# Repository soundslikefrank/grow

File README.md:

# GROW

A Eurorack genetic sequencer.

This repository serves as the home for its MCU code and hardware schematics.

There will be a lot more info soon.

## To build

```sh
git submodule update --init --recursive # if not cloned recursively
brew install cmake
brew install --cask gcc-arm-embedded
mkdir build && cd build
cmake -DCMAKE_TOOLCHAIN_FILE=../arm-none-eabi-gcc.cmake ..
make
```

## LICENSE

GNU General Public License v3.0

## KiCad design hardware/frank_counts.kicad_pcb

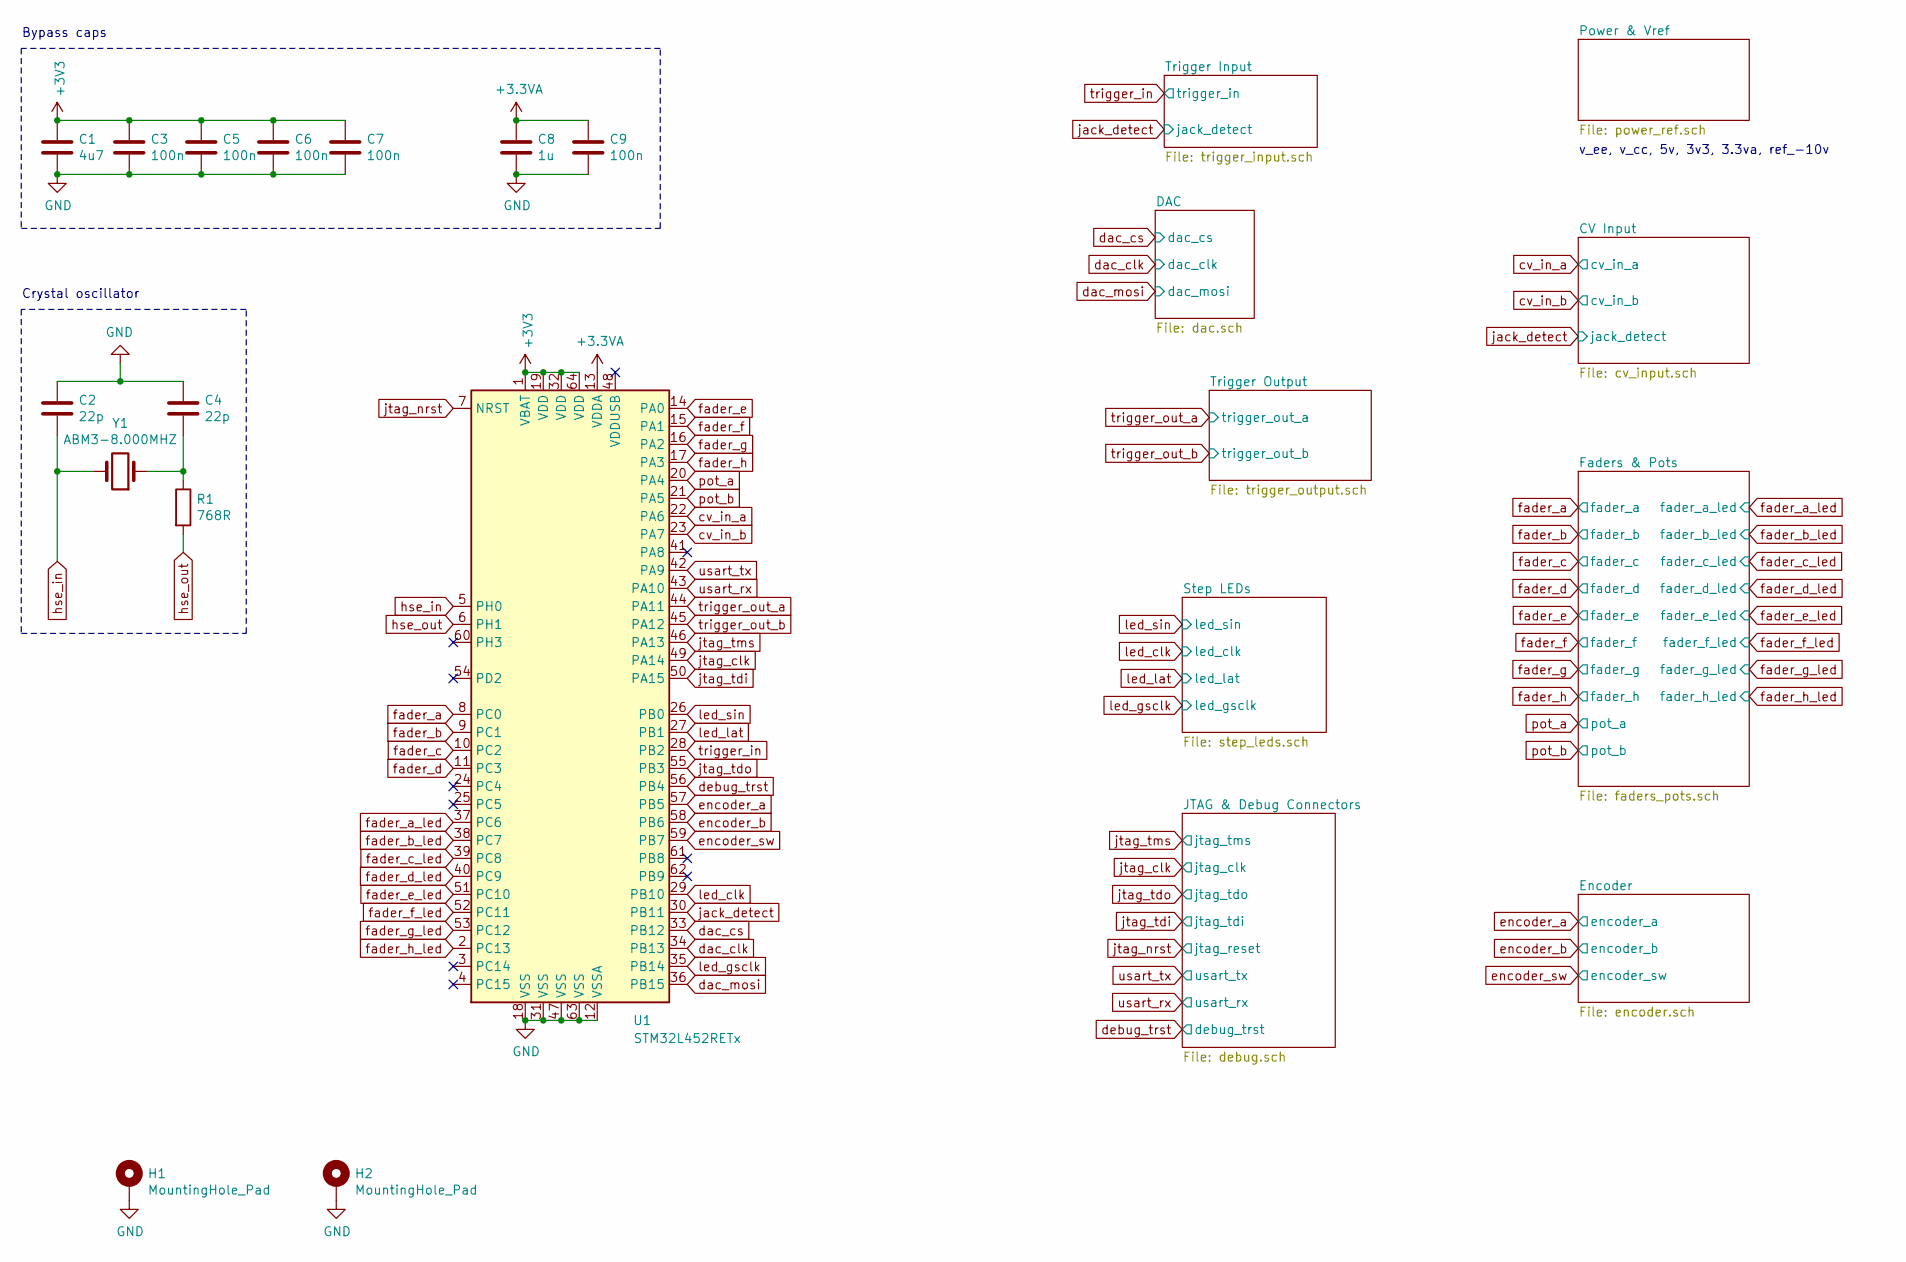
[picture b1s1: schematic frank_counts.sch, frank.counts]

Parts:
C1: 4u7; C_0603_1608Metric
C2, C4: 22p; C_0603_1608Metric
C3, C5, C6, C7, C9: 100n; C_0603_1608Metric
C8: 1u; C_0603_1608Metric
H1, H2: MountingHole_Pad; MountingHole_3.2mm_M3
R1: 768R; R_0603_1608Metric
U1: STM32L452RETx; LQFP-64_10x10mm_P0.5mm
Y1: ABM3-8.000MHZ; Crystal_SMD_Abracon_ABM3-2Pin_5.0x3.2mm_HandSoldering

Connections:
GND: C1.2, C2.1, C3.2, C4.1, C5.2, C6.2, C7.2, C8.2, C9.2, H1.1, H2.1, U1.12 (VSSA), U1.18 (VSS), U1.31 (VSS), U1.47 (VSS), U1.63 (VSS); also elsewhere on the board
unnamed: C4.2, R1.1, Y1.1
cv_in_a: U1.22 (PA6); also elsewhere on the board
cv_in_b: U1.23 (PA7); also elsewhere on the board
dac_avdd: C8.1, C9.1, U1.13 (VDDA); also elsewhere on the board
dac_clk: U1.34 (PB13); also elsewhere on the board
dac_cs: U1.33 (PB12); also elsewhere on the board
dac_mosi: U1.36 (PB15); also elsewhere on the board
debug_trst: U1.56 (PB4); also elsewhere on the board
encoder_a: U1.57 (PB5); also elsewhere on the board
encoder_b: U1.58 (PB6); also elsewhere on the board
encoder_sw: U1.59 (PB7); also elsewhere on the board
fader_a: U1.8 (PC0); also elsewhere on the board
fader_a_led: U1.37 (PC6); also elsewhere on the board
fader_b: U1.9 (PC1); also elsewhere on the board
fader_b_led: U1.38 (PC7); also elsewhere on the board
fader_c: U1.10 (PC2); also elsewhere on the board
fader_c_led: U1.39 (PC8); also elsewhere on the board
fader_d: U1.11 (PC3); also elsewhere on the board
fader_d_led: U1.40 (PC9); also elsewhere on the board
fader_e: U1.14 (PA0); also elsewhere on the board
fader_e_led: U1.51 (PC10); also elsewhere on the board
fader_f: U1.15 (PA1); also elsewhere on the board
fader_f_led: U1.52 (PC11); also elsewhere on the board
fader_g: U1.16 (PA2); also elsewhere on the board
fader_g_led: U1.53 (PC12); also elsewhere on the board
fader_h: U1.17 (PA3); also elsewhere on the board
fader_h_led: U1.2 (PC13); also elsewhere on the board
hse_in: C2.2, U1.5 (PH0), Y1.2
hse_out: R1.2, U1.6 (PH1)
jack_detect: U1.30 (PB11); also elsewhere on the board
jtag_clk: U1.49 (PA14); also elsewhere on the board
jtag_nrst: U1.7 (NRST); also elsewhere on the board
jtag_tdi: U1.50 (PA15); also elsewhere on the board
jtag_tdo: U1.55 (PB3); also elsewhere on the board
jtag_tms: U1.46 (PA13); also elsewhere on the board
led_clk: U1.29 (PB10); also elsewhere on the board
led_gsclk: U1.35 (PB14); also elsewhere on the board
led_lat: U1.27 (PB1); also elsewhere on the board
led_sin: U1.26 (PB0); also elsewhere on the board
pot_a: U1.20 (PA4); also elsewhere on the board
pot_b: U1.21 (PA5); also elsewhere on the board
trigger_in: U1.28 (PB2); also elsewhere on the board
trigger_out_a: U1.44 (PA11); also elsewhere on the board
trigger_out_b: U1.45 (PA12); also elsewhere on the board
usart_rx: U1.43 (PA10); also elsewhere on the board
usart_tx: U1.42 (PA9); also elsewhere on the board

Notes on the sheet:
Bypass caps
Crystal oscillator
v_ee, v_cc, 5v, 3v3, 3.3va, ref_-10v

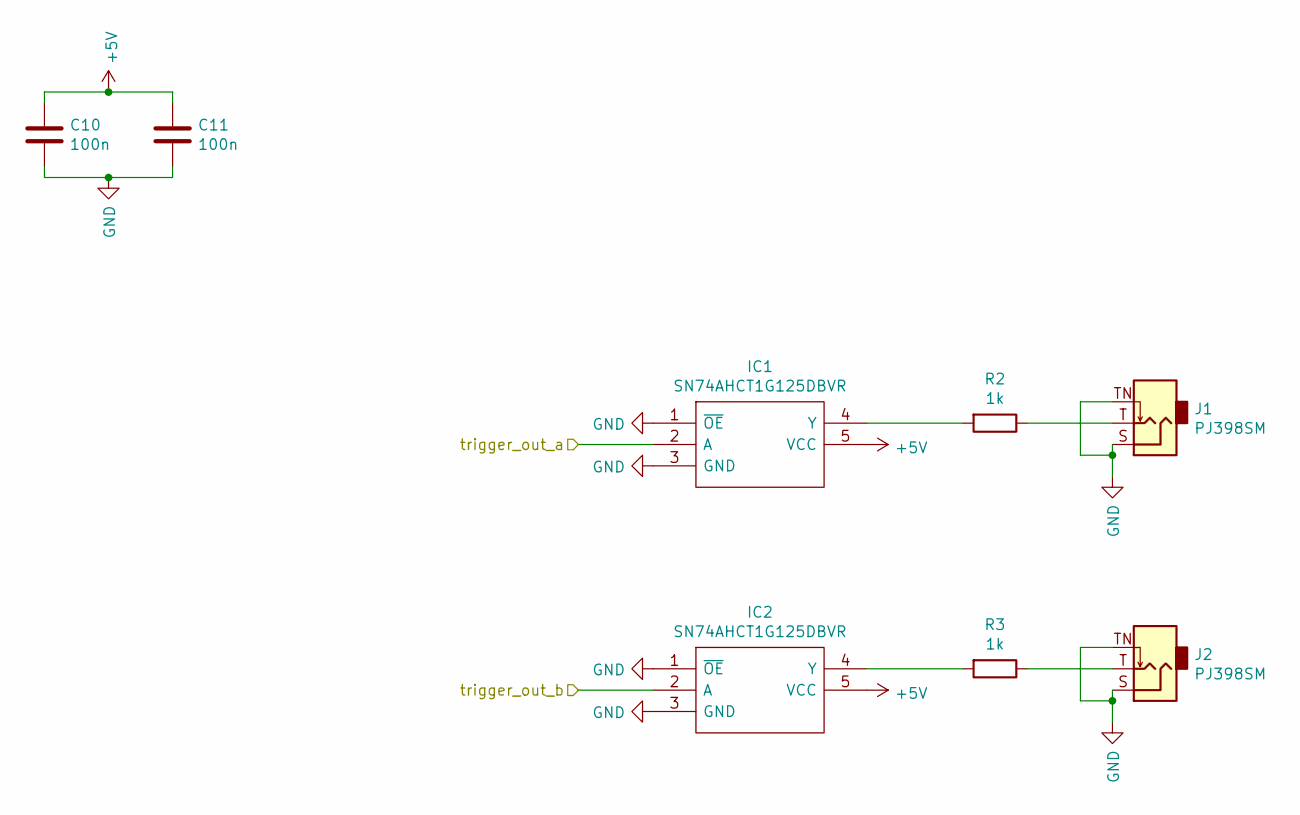
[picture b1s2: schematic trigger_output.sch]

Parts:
C10, C11: 100n; C_0603_1608Metric
IC1, IC2: SN74AHCT1G125DBVR; SOT95P280X145-5N; Manufacturer_Part_Number SN74AHCT1G125DBVR; Mouser Part Number 595-SNAHCT1G125DBVR
J1, J2: PJ398SM; Jack_3.5mm_QingPu_WQP-PJ398SM_Vertical_CircularHoles
R2, R3: 1k; R_0603_1608Metric

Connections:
+5V: C10.1, C11.1, IC1.5 (VCC), IC2.5 (VCC); also elsewhere on the board
GND: C10.2, C11.2, IC1.1 (~OE), IC1.3 (GND), IC2.1 (~OE), IC2.3 (GND), J1.S, J1.TN, J2.S, J2.TN; also elsewhere on the board
unnamed: IC1.4 (Y), R2.2
unnamed: IC2.4 (Y), R3.2
unnamed: J1.T, R2.1
unnamed: J2.T, R3.1
trigger_out_a: IC1.2 (A); also elsewhere on the board
trigger_out_b: IC2.2 (A); also elsewhere on the board

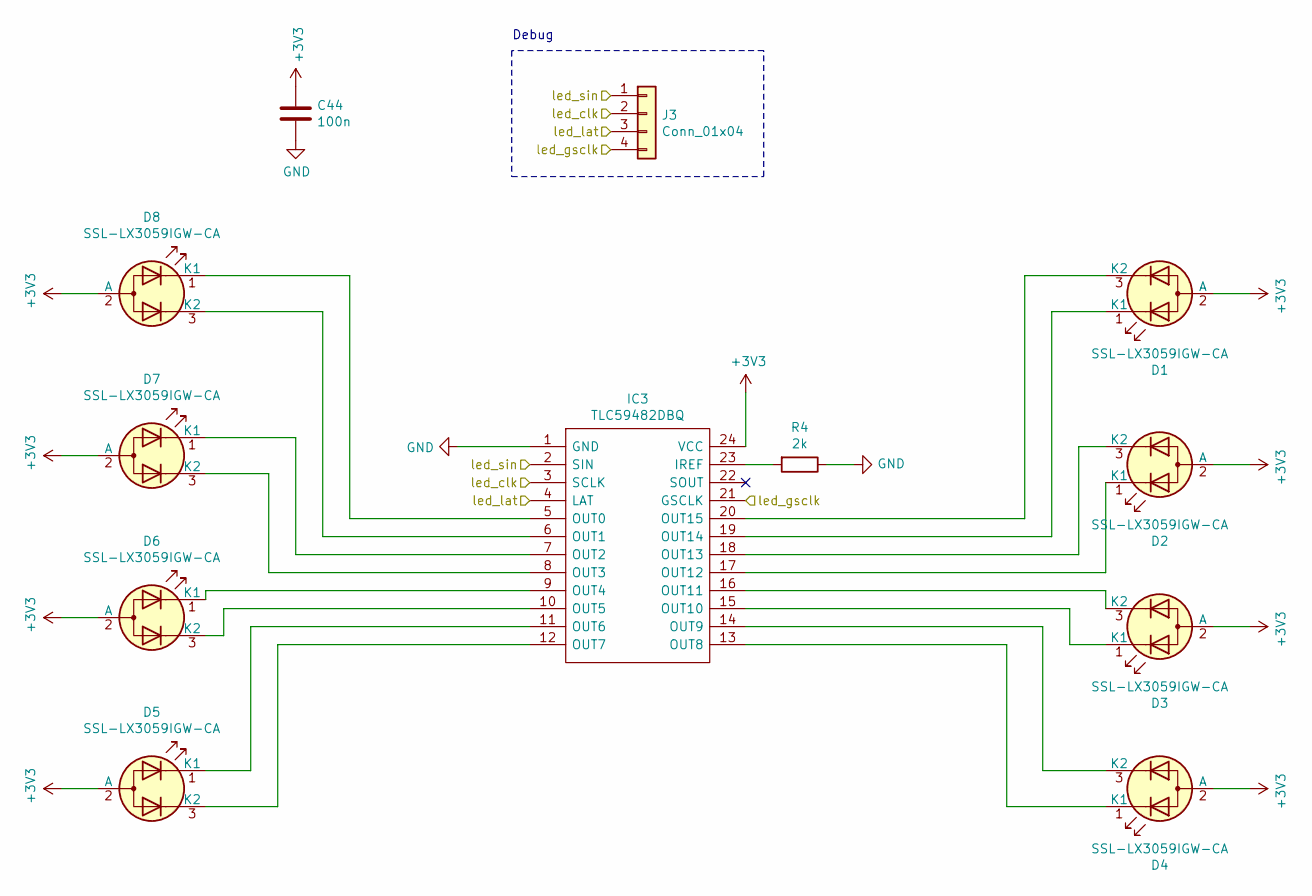
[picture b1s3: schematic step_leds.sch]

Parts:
C44: 100n; C_0603_1608Metric
D1, D2, D3, D4, D5, D6, D7, D8: SSL-LX3059IGW-CA; LED_D3.0mm-3
IC3: TLC59482DBQ; SOP64P600X175-24N; Manufacturer_Part_Number TLC59482DBQ; Mouser Part Number 595-TLC59482DBQ
J3: Conn_01x04; PinHeader_1x04_P2.54mm_Vertical
R4: 2k; R_0603_1608Metric

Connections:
GND: C44.2, IC3.1 (GND), R4.1; also elsewhere on the board
unnamed: D1.1 (K1), IC3.19 (OUT14)
unnamed: D1.3 (K2), IC3.20 (OUT15)
unnamed: D2.1 (K1), IC3.17 (OUT12)
unnamed: D2.3 (K2), IC3.18 (OUT13)
unnamed: D3.1 (K1), IC3.15 (OUT10)
unnamed: D3.3 (K2), IC3.16 (OUT11)
unnamed: D4.1 (K1), IC3.13 (OUT8)
unnamed: D4.3 (K2), IC3.14 (OUT9)
unnamed: D5.1 (K1), IC3.11 (OUT6)
unnamed: D5.3 (K2), IC3.12 (OUT7)
unnamed: D6.1 (K1), IC3.9 (OUT4)
unnamed: D6.3 (K2), IC3.10 (OUT5)
unnamed: D7.1 (K1), IC3.7 (OUT2)
unnamed: D7.3 (K2), IC3.8 (OUT3)
unnamed: D8.1 (K1), IC3.5 (OUT0)
unnamed: D8.3 (K2), IC3.6 (OUT1)
unnamed: IC3.23 (IREF), R4.2
led_clk: IC3.3 (SCLK), J3.2; also elsewhere on the board
led_gsclk: IC3.21 (GSCLK), J3.4; also elsewhere on the board
led_lat: IC3.4 (LAT), J3.3; also elsewhere on the board
led_sin: IC3.2 (SIN), J3.1; also elsewhere on the board

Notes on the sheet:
Debug

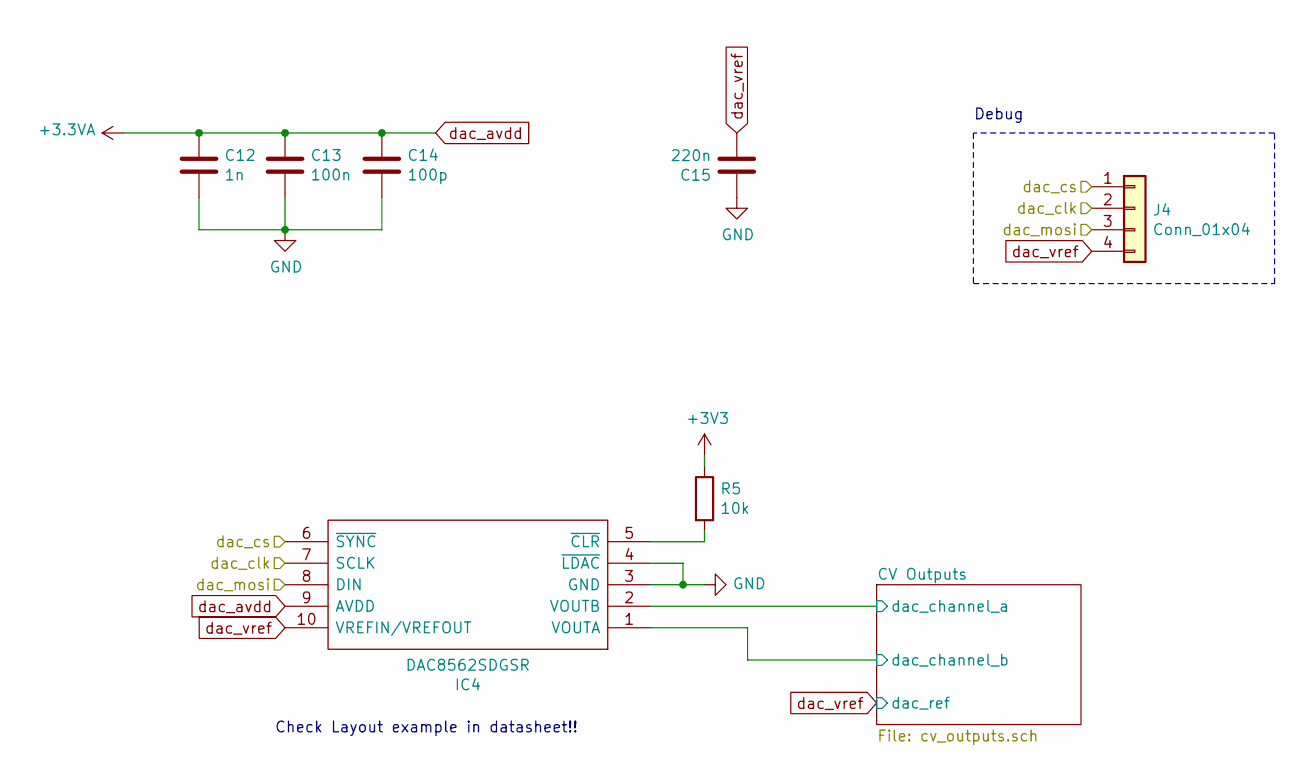
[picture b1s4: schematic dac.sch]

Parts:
C12: 1n; C_0603_1608Metric
C13: 100n; C_0603_1608Metric
C14: 100p; C_0603_1608Metric
C15: 220n; C_0603_1608Metric
IC4: DAC8562SDGSR; SOP50P490X110-10N; Manufacturer_Part_Number DAC8562SDGSR; Mouser Part Number 595-DAC8562SDGSR
J4: Conn_01x04; PinHeader_1x04_P2.54mm_Vertical
R5: 10k; R_0603_1608Metric

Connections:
/DAC/CV Outputs/dac_channel_a: IC4.2 (VOUTB); also elsewhere on the board
/DAC/CV Outputs/dac_channel_b: IC4.1 (VOUTA); also elsewhere on the board
GND: C12.1, C13.2, C14.2, C15.2, IC4.3 (GND), IC4.4 (~LDAC); also elsewhere on the board
unnamed: IC4.5 (~CLR), R5.2
dac_avdd: C12.2, C13.1, C14.1, IC4.9 (AVDD); also elsewhere on the board
dac_clk: IC4.7 (SCLK), J4.2; also elsewhere on the board
dac_cs: IC4.6 (~SYNC), J4.1; also elsewhere on the board
dac_mosi: IC4.8 (DIN), J4.3; also elsewhere on the board
dac_vref: C15.1, IC4.10 (VREFIN/VREFOUT), J4.4; also elsewhere on the board

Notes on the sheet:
Check Layout example in datasheet!!
Debug

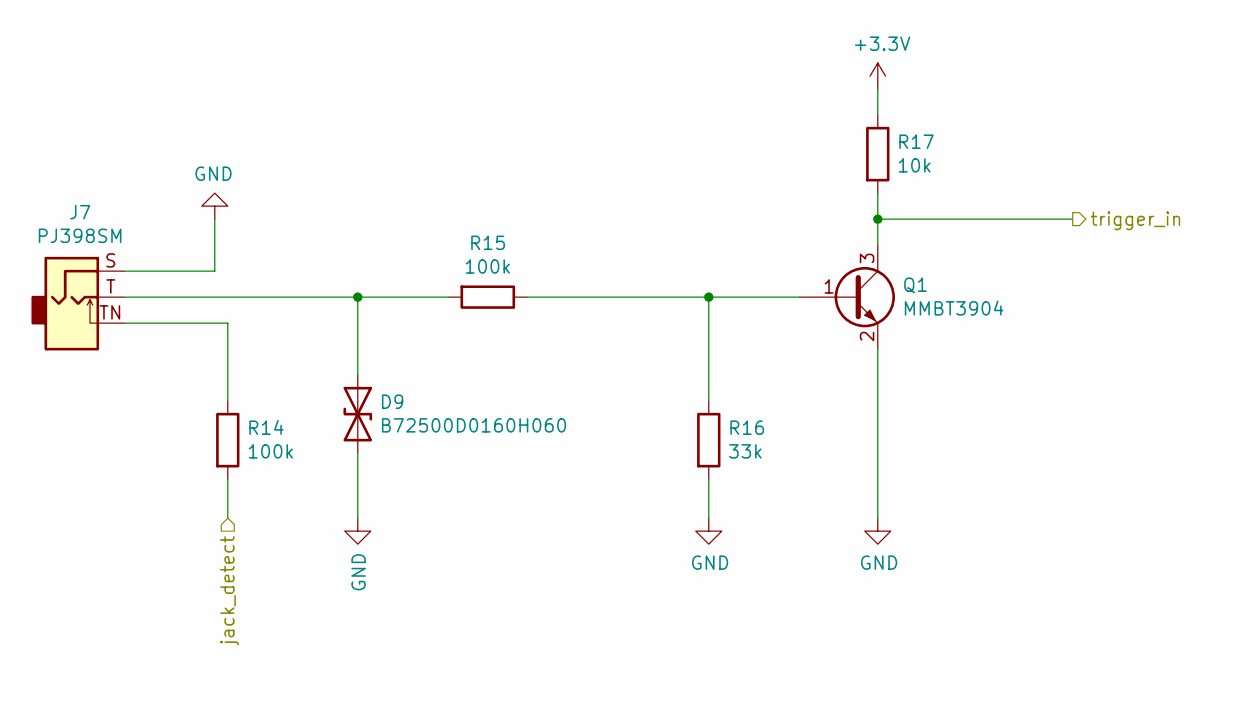
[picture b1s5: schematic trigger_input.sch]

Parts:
D9: B72500D0160H060; D_0603_1608Metric
J7: PJ398SM; Jack_3.5mm_QingPu_WQP-PJ398SM_Vertical_CircularHoles
Q1: MMBT3904; SOT-23
R14, R15: 100k; R_0603_1608Metric
R16: 33k; R_0603_1608Metric
R17: 10k; R_0603_1608Metric

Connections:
GND: D9.2 (A2), J7.S, Q1.2 (E), R16.2; also elsewhere on the board
unnamed: D9.1 (A1), J7.T, R15.2
unnamed: J7.TN, R14.1
unnamed: Q1.1 (B), R15.1, R16.1
jack_detect: R14.2; also elsewhere on the board
trigger_in: Q1.3 (C), R17.2; also elsewhere on the board

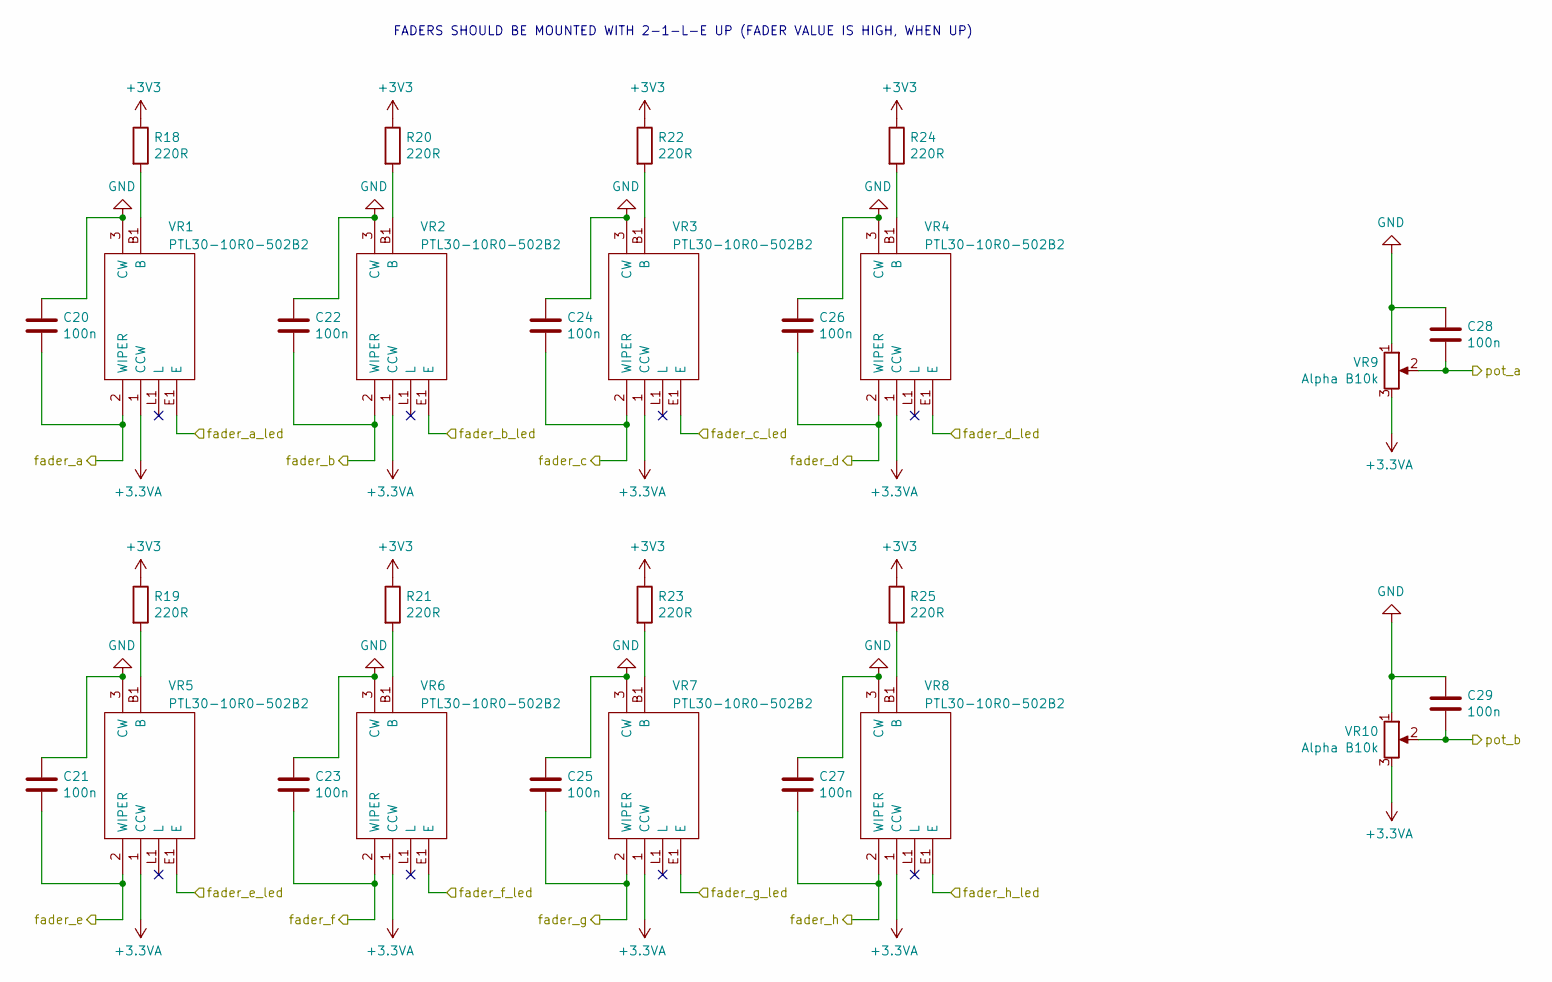
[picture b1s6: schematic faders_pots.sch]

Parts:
C20, C21, C22, C23, C24, C25, C26, C27, C28, C29: 100n; C_0603_1608Metric
R18, R19, R20, R21, R22, R23, R24, R25: 220R; R_0603_1608Metric
VR1, VR2, VR3, VR4, VR5, VR6, VR7, VR8: PTL30-10R0-502B2; PTL3010R1103B2; Manufacturer_Part_Number PTL30-10R0-502B2; Mouser Part Number 652-PTL30-10R0-502B2
VR9, VR10: Alpha B10k; Potentiometer_Alpha_RD901F-40-00D_Single_Vertical

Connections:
GND: C20.1, C21.1, C22.1, C23.1, C24.1, C25.1, C26.1, C27.1, C28.1, C29.1, VR1.3 (CW), VR2.3 (CW), VR3.3 (CW), VR4.3 (CW), VR5.3 (CW), VR6.3 (CW), VR7.3 (CW), VR8.3 (CW), VR9.1, VR10.1; also elsewhere on the board
unnamed: R18.2, VR1.B1 (B)
unnamed: R19.2, VR5.B1 (B)
unnamed: R20.2, VR2.B1 (B)
unnamed: R21.2, VR6.B1 (B)
unnamed: R22.2, VR3.B1 (B)
unnamed: R23.2, VR7.B1 (B)
unnamed: R24.2, VR4.B1 (B)
unnamed: R25.2, VR8.B1 (B)
dac_avdd: VR1.1 (CCW), VR2.1 (CCW), VR3.1 (CCW), VR4.1 (CCW), VR5.1 (CCW), VR6.1 (CCW), VR7.1 (CCW), VR8.1 (CCW), VR9.3, VR10.3; also elsewhere on the board
fader_a: C20.2, VR1.2 (WIPER); also elsewhere on the board
fader_a_led: VR1.E1 (E); also elsewhere on the board
fader_b: C22.2, VR2.2 (WIPER); also elsewhere on the board
fader_b_led: VR2.E1 (E); also elsewhere on the board
fader_c: C24.2, VR3.2 (WIPER); also elsewhere on the board
fader_c_led: VR3.E1 (E); also elsewhere on the board
fader_d: C26.2, VR4.2 (WIPER); also elsewhere on the board
fader_d_led: VR4.E1 (E); also elsewhere on the board
fader_e: C21.2, VR5.2 (WIPER); also elsewhere on the board
fader_e_led: VR5.E1 (E); also elsewhere on the board
fader_f: C23.2, VR6.2 (WIPER); also elsewhere on the board
fader_f_led: VR6.E1 (E); also elsewhere on the board
fader_g: C25.2, VR7.2 (WIPER); also elsewhere on the board
fader_g_led: VR7.E1 (E); also elsewhere on the board
fader_h: C27.2, VR8.2 (WIPER); also elsewhere on the board
fader_h_led: VR8.E1 (E); also elsewhere on the board
pot_a: C28.2, VR9.2; also elsewhere on the board
pot_b: C29.2, VR10.2; also elsewhere on the board

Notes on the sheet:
FADERS SHOULD BE MOUNTED WITH 2-1-L-E UP (FADER VALUE IS HIGH, WHEN UP)

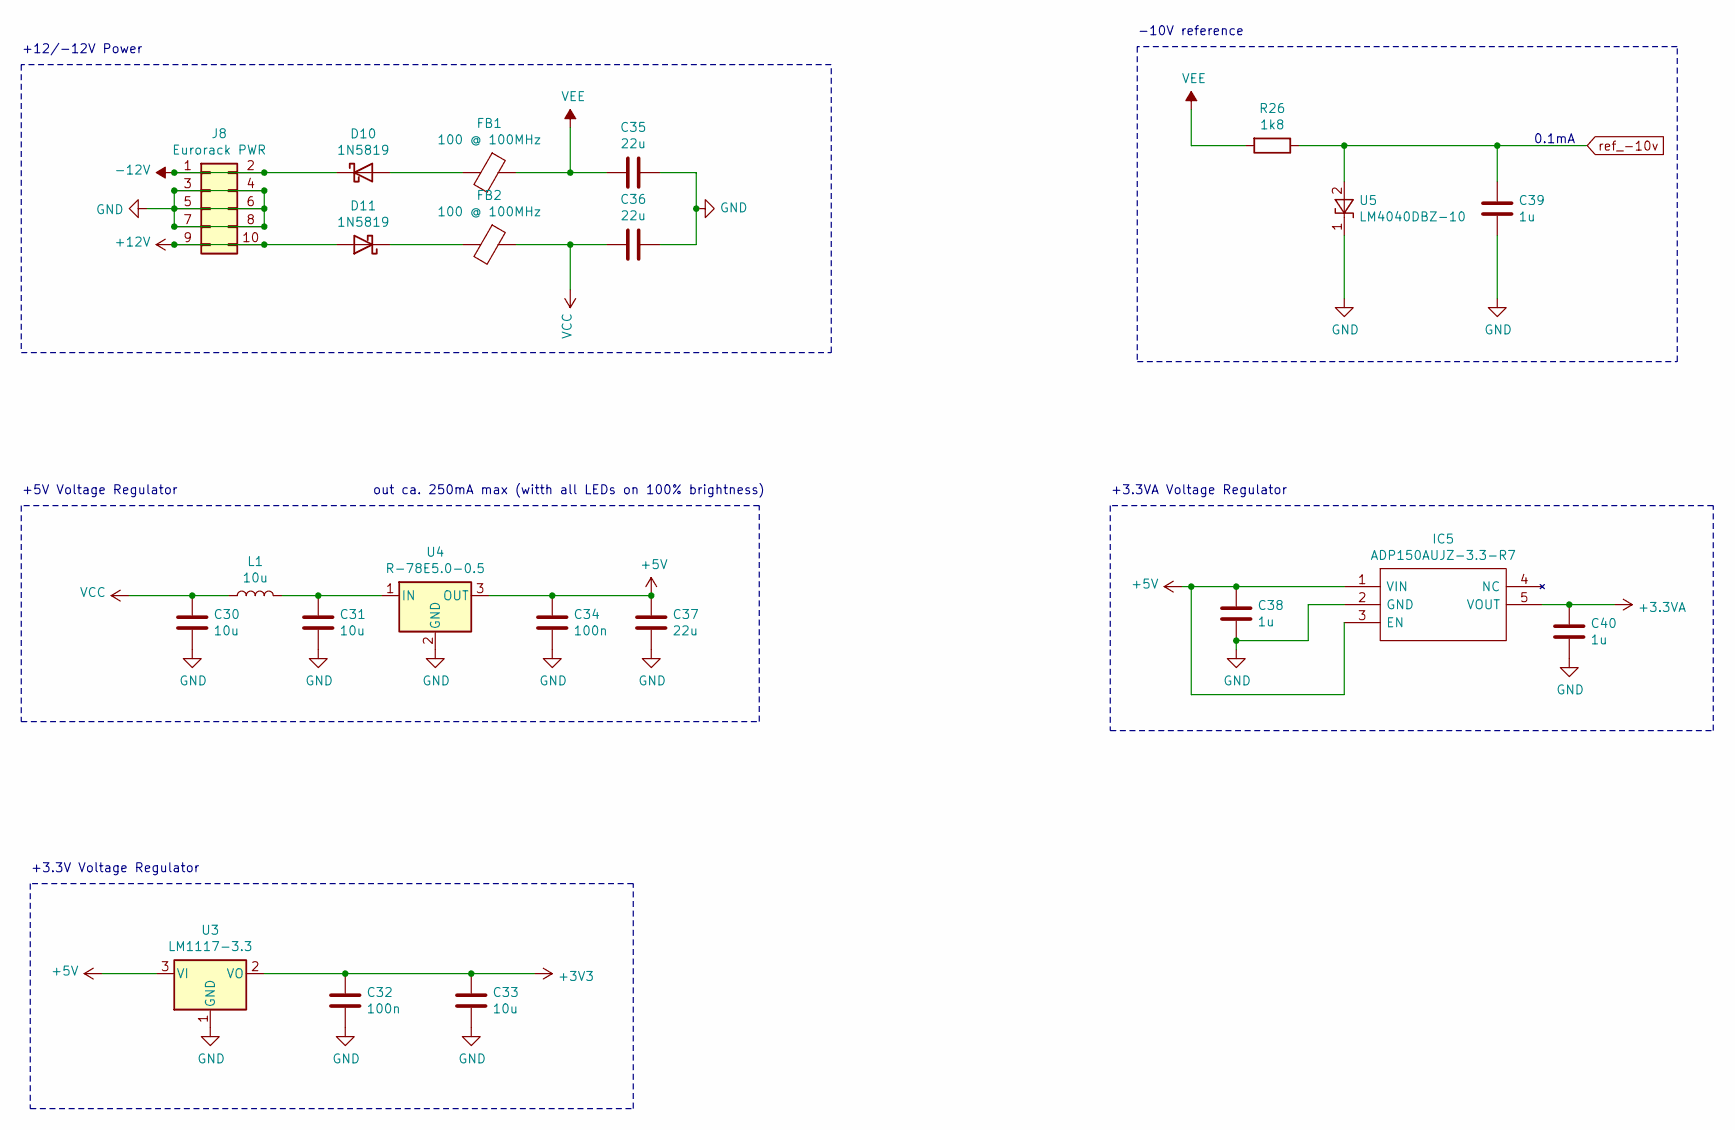
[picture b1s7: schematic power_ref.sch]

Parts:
C30, C31, C33: 10u; C_0805_2012Metric
C32, C34: 100n; C_0603_1608Metric
C35, C36, C37: 22u; C_0805_2012Metric
C38, C39, C40: 1u; C_0603_1608Metric
D10, D11: 1N5819; D_SOD-123
FB1, FB2: 100 @ 100MHz; L_0805_2012Metric
IC5: ADP150AUJZ-3.3-R7; SOT95P280X100-5N; Manufacturer_Part_Number ADP150AUJZ-3.3-R7; Mouser Part Number 584-ADP150AUJZ-3.3R7
J8: Eurorack PWR; IDC-Header_2x05_P2.54mm_Vertical
L1: 10u; L_0805_2012Metric
R26: 1k8; R_0603_1608Metric
U3: LM1117-3.3; SOT-223
U4: R-78E5.0-0.5; Converter_DCDC_RECOM_R-78E-0.5_THT
U5: LM4040DBZ-10; SOT-23

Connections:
+5V: C34.1, C37.2, C38.1, IC5.1 (VIN), IC5.3 (EN), U3.3 (VI), U4.3 (OUT); also elsewhere on the board
+12V: D11.2 (A), J8.9, J8.10
-12V: D10.1 (K), J8.1, J8.2
GND: C30.2, C31.1, C32.2, C33.2, C34.2, C35.1, C36.1, C37.1, C38.2, C39.2, C40.2, IC5.2 (GND), J8.3, J8.4, J8.5, J8.6, J8.7, J8.8, U3.1 (GND), U4.2 (GND), U5.1 (K); also elsewhere on the board
unnamed: C31.2, L1.2, U4.1 (IN)
unnamed: D10.2 (A), FB1.2
unnamed: D11.1 (K), FB2.2
VCC: C30.1, C36.2, FB2.1, L1.1; also elsewhere on the board
VEE: C35.2, FB1.1, R26.2; also elsewhere on the board
dac_avdd: C40.1, IC5.5 (VOUT); also elsewhere on the board
ref_-10v: C39.1, R26.1, U5.2 (A); also elsewhere on the board

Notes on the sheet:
-10V reference
0.1mA
+5V Voltage Regulator
+12/-12V Power
+3.3V Voltage Regulator
out ca. 250mA max (witth all LEDs on 100% brightness)
+3.3VA Voltage Regulator

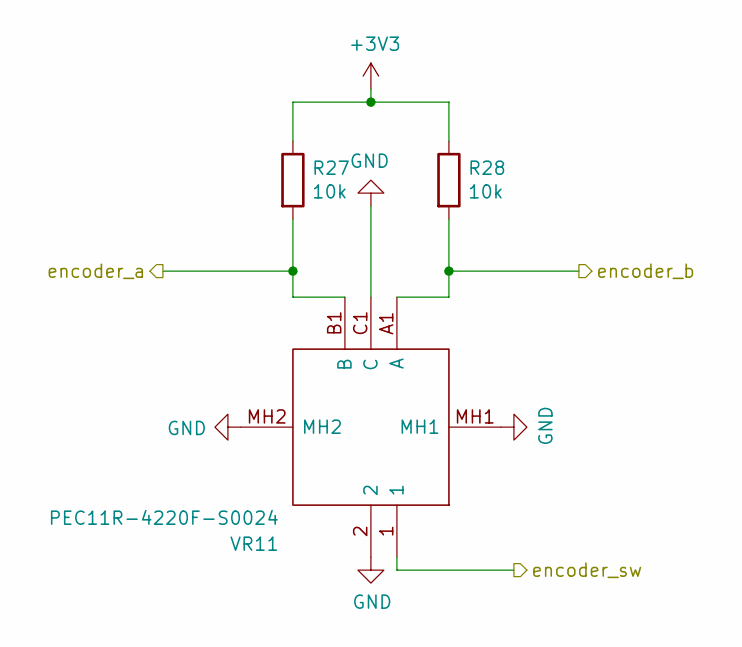
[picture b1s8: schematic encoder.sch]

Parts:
R27, R28: 10k; R_0603_1608Metric
VR11: PEC11R-4220F-S0024; PEC11R4220FS0024; Manufacturer_Part_Number PEC11R-4220F-S0024; Mouser Part Number 652-PEC11R-4220F-S24

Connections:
GND: VR11.2, VR11.C1 (C), VR11.MH1, VR11.MH2; also elsewhere on the board
encoder_a: R27.2, VR11.B1 (B); also elsewhere on the board
encoder_b: R28.2, VR11.A1 (A); also elsewhere on the board
encoder_sw: VR11.1; also elsewhere on the board

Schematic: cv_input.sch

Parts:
C41, C42: 100p; C_0603_1608Metric
C43: 100n; C_0603_1608Metric
D12, D13: B72500D0160H060; D_0603_1608Metric
J9, J10: PJ398SM; Jack_3.5mm_QingPu_WQP-PJ398SM_Vertical_CircularHoles
R29, R30: 100k; R_0603_1608Metric
R31, R32: 140k; R_0603_1608Metric
R33, R34: 200k; R_0603_1608Metric
R35, R36: 33k; R_0603_1608Metric
R37, R38: 100R; R_0603_1608Metric
U6: MCP6002-xMS; SOIC-8_3.9x4.9mm_P1.27mm

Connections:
GND: C43.2, D12.2 (A2), D13.2 (A2), J9.S, J10.S, U6.3 (+), U6.4 (V-), U6.5 (+); also elsewhere on the board
unnamed: C41.1, R31.1, R33.2, R35.2, U6.2 (-)
unnamed: C41.2, R35.1, R37.2, U6.1
unnamed: C42.1, R32.1, R34.2, R36.2, U6.6 (-)
unnamed: C42.2, R36.1, R38.2, U6.7
unnamed: D12.1 (A1), J9.T, R31.2
unnamed: D13.1 (A1), J10.T, R32.2
unnamed: J9.TN, R29.1
unnamed: J10.TN, R30.1
cv_in_a: R37.1; also elsewhere on the board
cv_in_b: R38.1; also elsewhere on the board
jack_detect: R29.2, R30.2; also elsewhere on the board
ref_-10v: R33.1, R34.1; also elsewhere on the board

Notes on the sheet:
-7V-+7V

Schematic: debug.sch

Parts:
J11: Conn_02x05_Odd_Even; PinHeader_2x05_P1.27mm_Vertical
J12: Conn_01x03; PinHeader_1x03_P2.54mm_Vertical
J13: Conn_01x01; PinHeader_1x01_P2.54mm_Vertical

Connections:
GND: J11.3, J11.5, J11.9, J12.3; also elsewhere on the board
debug_trst: J13.1; also elsewhere on the board
jtag_clk: J11.4; also elsewhere on the board
jtag_nrst: J11.10; also elsewhere on the board
jtag_tdi: J11.8; also elsewhere on the board
jtag_tdo: J11.6; also elsewhere on the board
jtag_tms: J11.2; also elsewhere on the board
usart_rx: J12.2; also elsewhere on the board
usart_tx: J12.1; also elsewhere on the board

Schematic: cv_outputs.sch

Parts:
C16, C17: 100n; C_0603_1608Metric
C18, C19: 7p; C_0603_1608Metric
J5, J6: PJ398SM; Jack_3.5mm_QingPu_WQP-PJ398SM_Vertical_CircularHoles
R6: 36k; R_0603_1608Metric
R7: 56k; R_0603_1608Metric
R8, R9: 75k; R_0603_1608Metric
R10, R11: 270k; R_0603_1608Metric
R12, R13: 500; R_0603_1608Metric
U2: TL072; SOIC-8_3.9x4.9mm_P1.27mm

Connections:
/DAC/CV Outputs/dac_channel_a: R8.2; also elsewhere on the board
/DAC/CV Outputs/dac_channel_b: R9.2; also elsewhere on the board
GND: C16.1, C17.1, J5.S, J5.TN, J6.S, J6.TN, R7.1; also elsewhere on the board
unnamed: C18.1, R12.2, U2.1
unnamed: C18.2, R8.1, R10.2, U2.2 (-)
unnamed: C19.1, R13.2, U2.7
unnamed: C19.2, R9.1, R11.2, U2.6 (-)
unnamed: J5.T, R10.1, R12.1
unnamed: J6.T, R11.1, R13.1
VCC: C16.2, U2.8 (V+); also elsewhere on the board
VEE: C17.2, U2.4 (V-); also elsewhere on the board
dac_vref: R6.2; also elsewhere on the board
ref_cv_out: R6.1, R7.2, U2.3 (+), U2.5 (+)

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
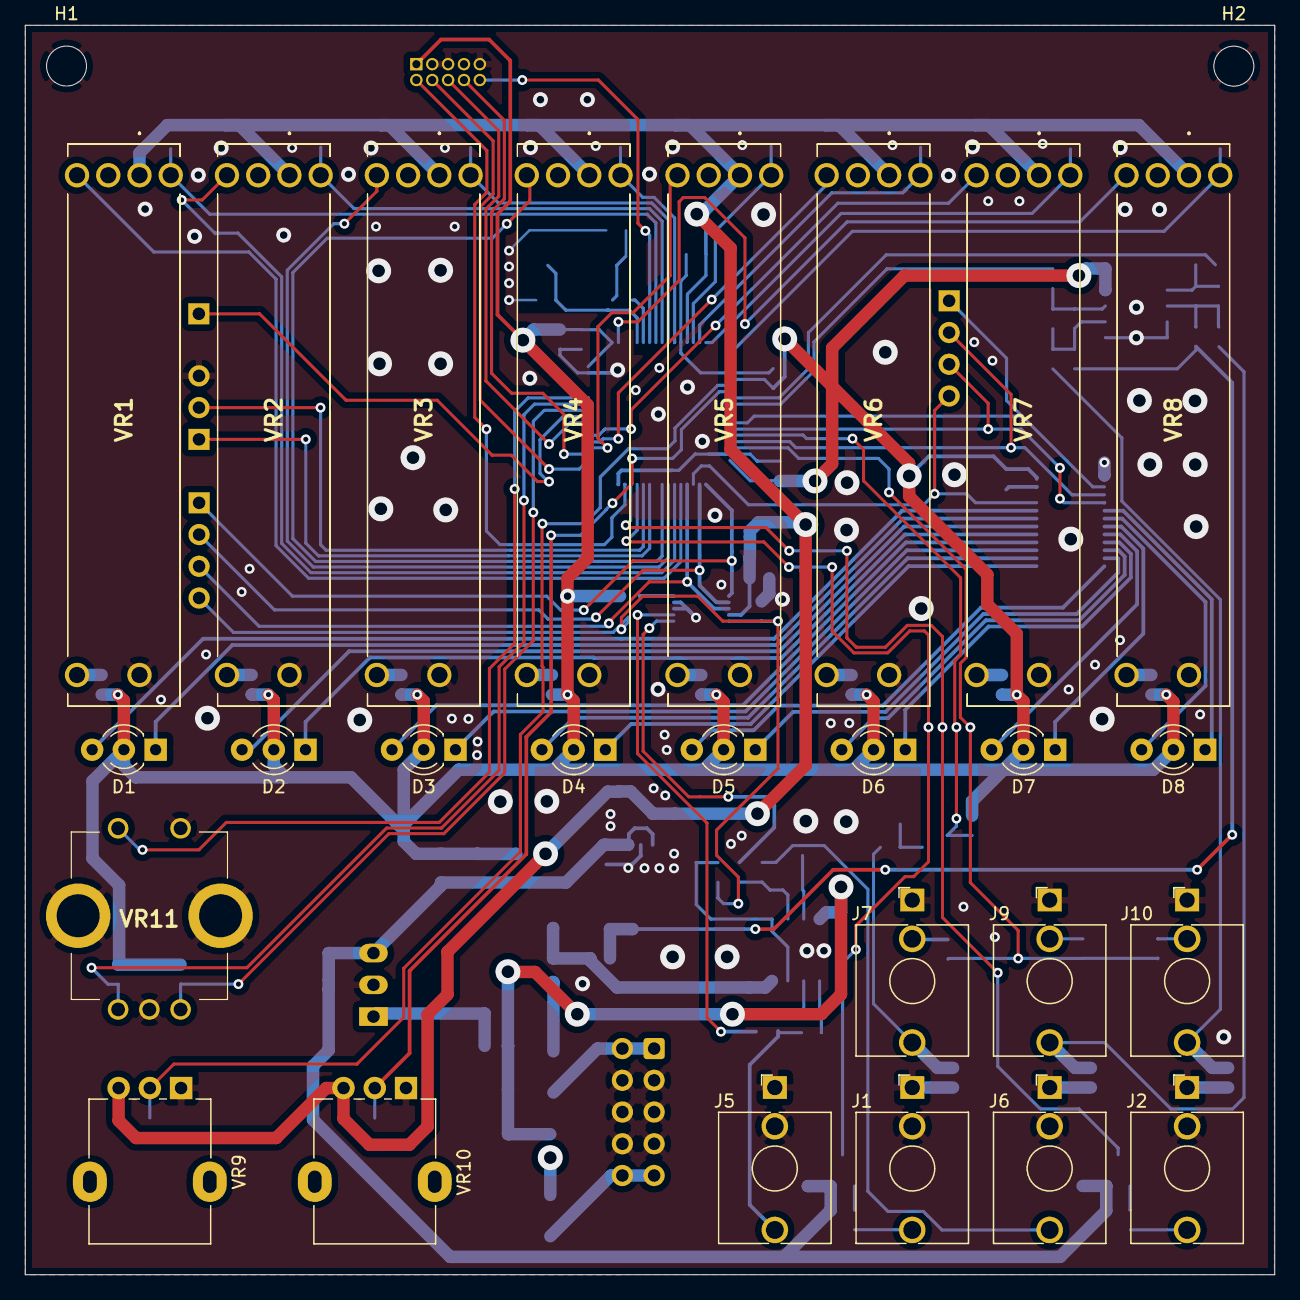
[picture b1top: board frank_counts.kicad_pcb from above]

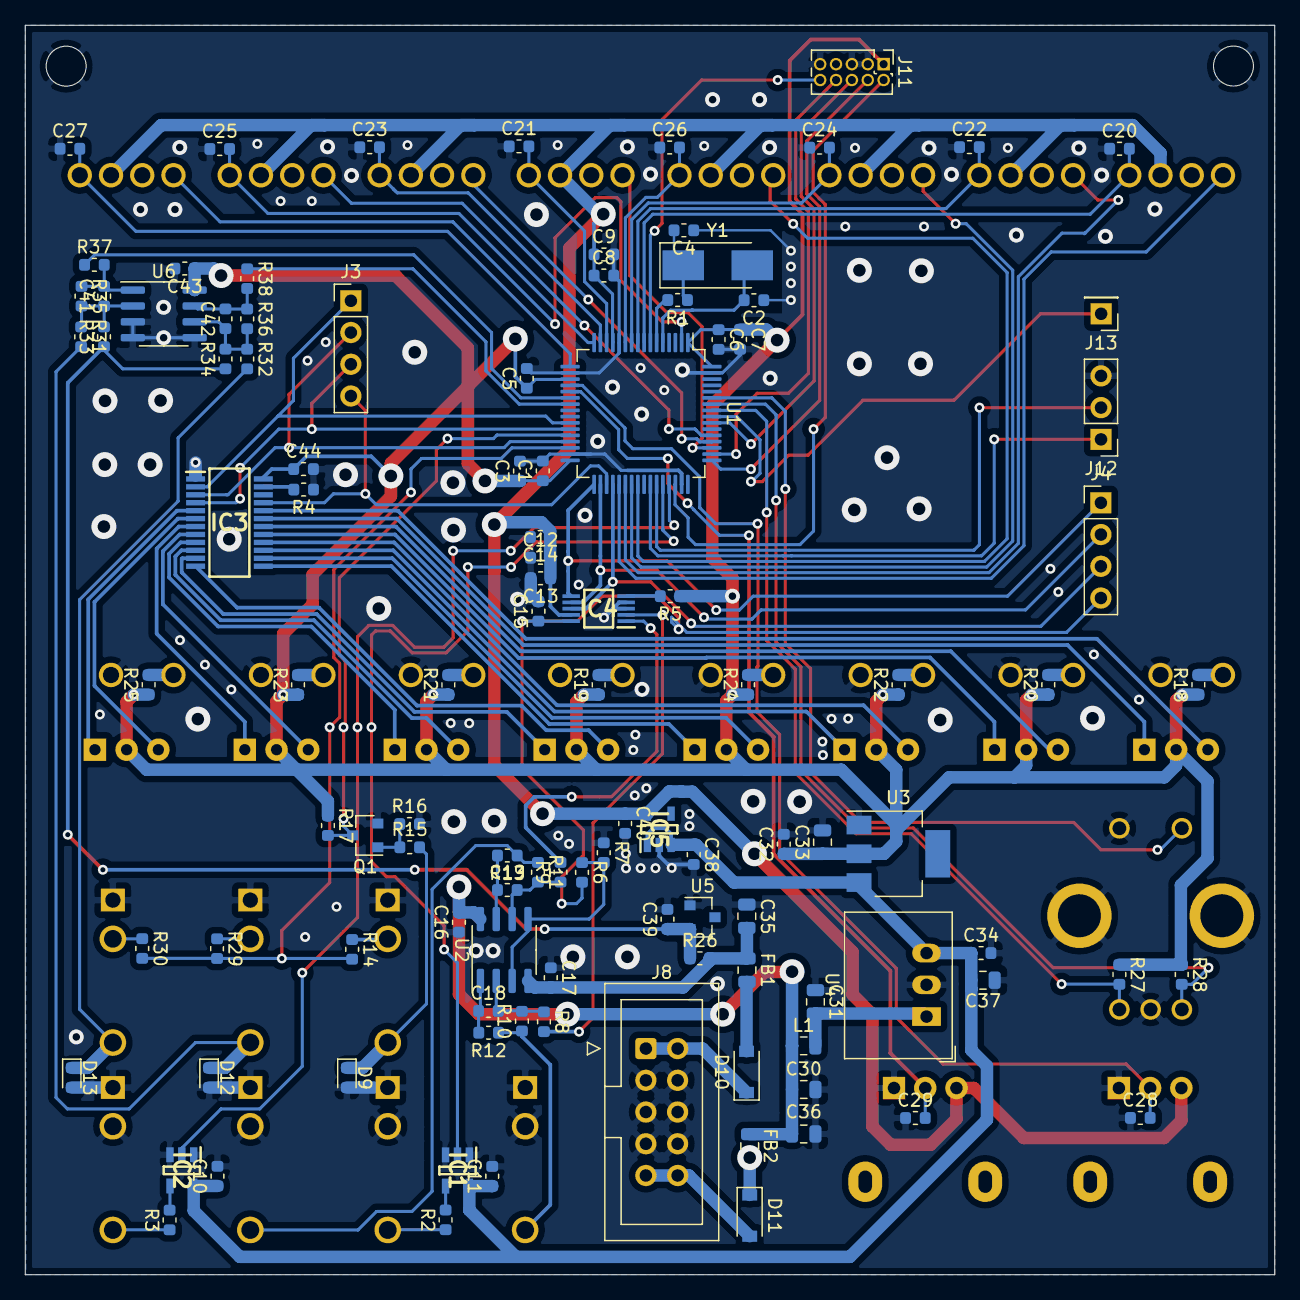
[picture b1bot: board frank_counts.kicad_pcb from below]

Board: 2 copper layers, 100.0 x 100.0 mm, 137 parts (109 on the bottom side), 108 nets.
